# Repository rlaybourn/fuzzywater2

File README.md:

# fuzzywater
This is a masters project to create a fuzzy logic based irrigation controller for greenhouse environments
The system is based on a raspberry pi master unit and pic based slave units

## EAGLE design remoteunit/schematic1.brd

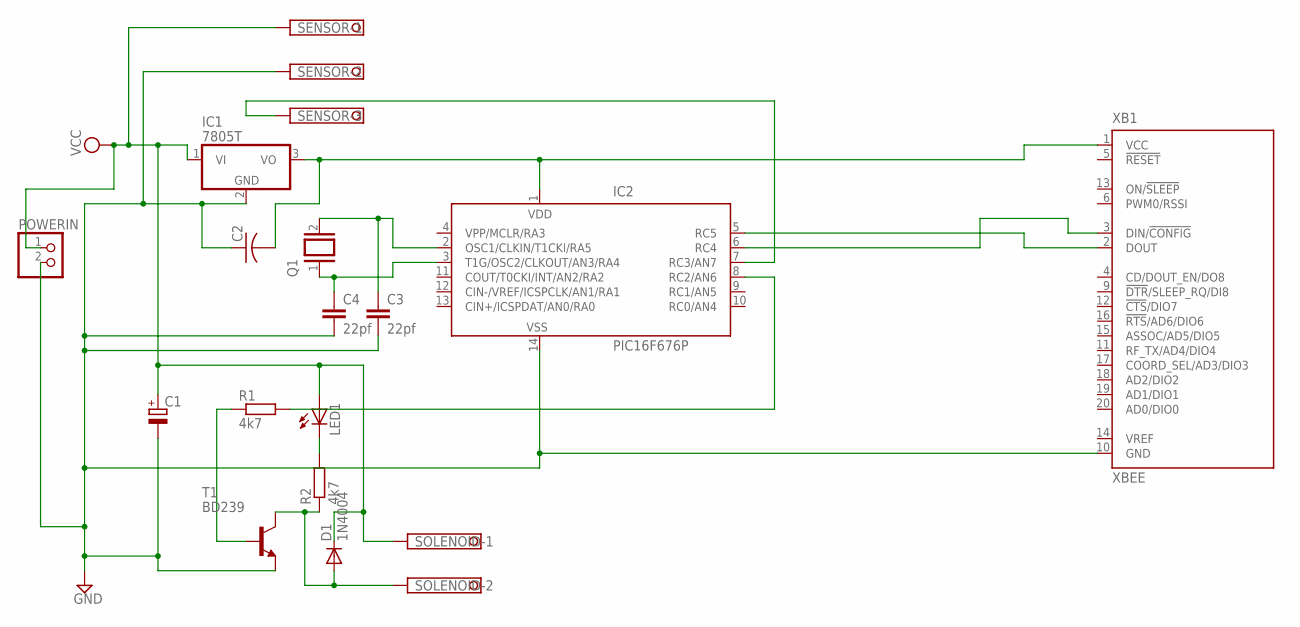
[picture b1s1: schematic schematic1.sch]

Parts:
C1: CPOL-EUE3.5-8; E3,5-8
C2: C-US050-024X044; C050-024X044
C3, C4: 22pf; C025-025X050
D1: 1N4004; DO41-10
IC1: 7805T; TO220H
IC2: PIC16F676P; DIL14
LED1: LED_ELD260; LED_LD260
POWERIN: PINHD-1X2; 1X02
Q1: XTAL; Q
R1, R2: 4k7; 0207/15
SENSOR: 1751251
SOLENOID: 1751248
T1: BD239; TO220
XB1: XBEE

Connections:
GND: C1.-, C2.1, C3.2, C4.2, IC1.2 (GND), IC2.14 (VSS), POWERIN.2, SENSOR.2, T1.3 (E), XB1.10 (GND)
unnamed: C2.2, IC1.3 (VO), IC2.1 (VDD), XB1.1 (VCC)
unnamed: IC2.8 (RC2/AN6), R1.2
unnamed: C3.1, IC2.2 (OSC1/CLKIN/T1CKI/RA5), Q1.2
unnamed: C4.1, IC2.3 (T1G/OSC2/CLKOUT/AN3/RA4), Q1.1
unnamed: IC2.5 (RC5), XB1.2 (DOUT)
unnamed: IC2.6 (RC4), XB1.3 (DIN/!CONFIG)
unnamed: D1.A, R2.1, SOLENOID.2, T1.2 (C)
unnamed: R1.1, T1.1 (B)
unnamed: LED1.K (C), R2.2
REGULATOR: IC2.7 (RC3/AN7), SENSOR.3
VCC: C1.+, D1.C, IC1.1 (VI), LED1.A, POWERIN.1, SENSOR.1, SOLENOID.1

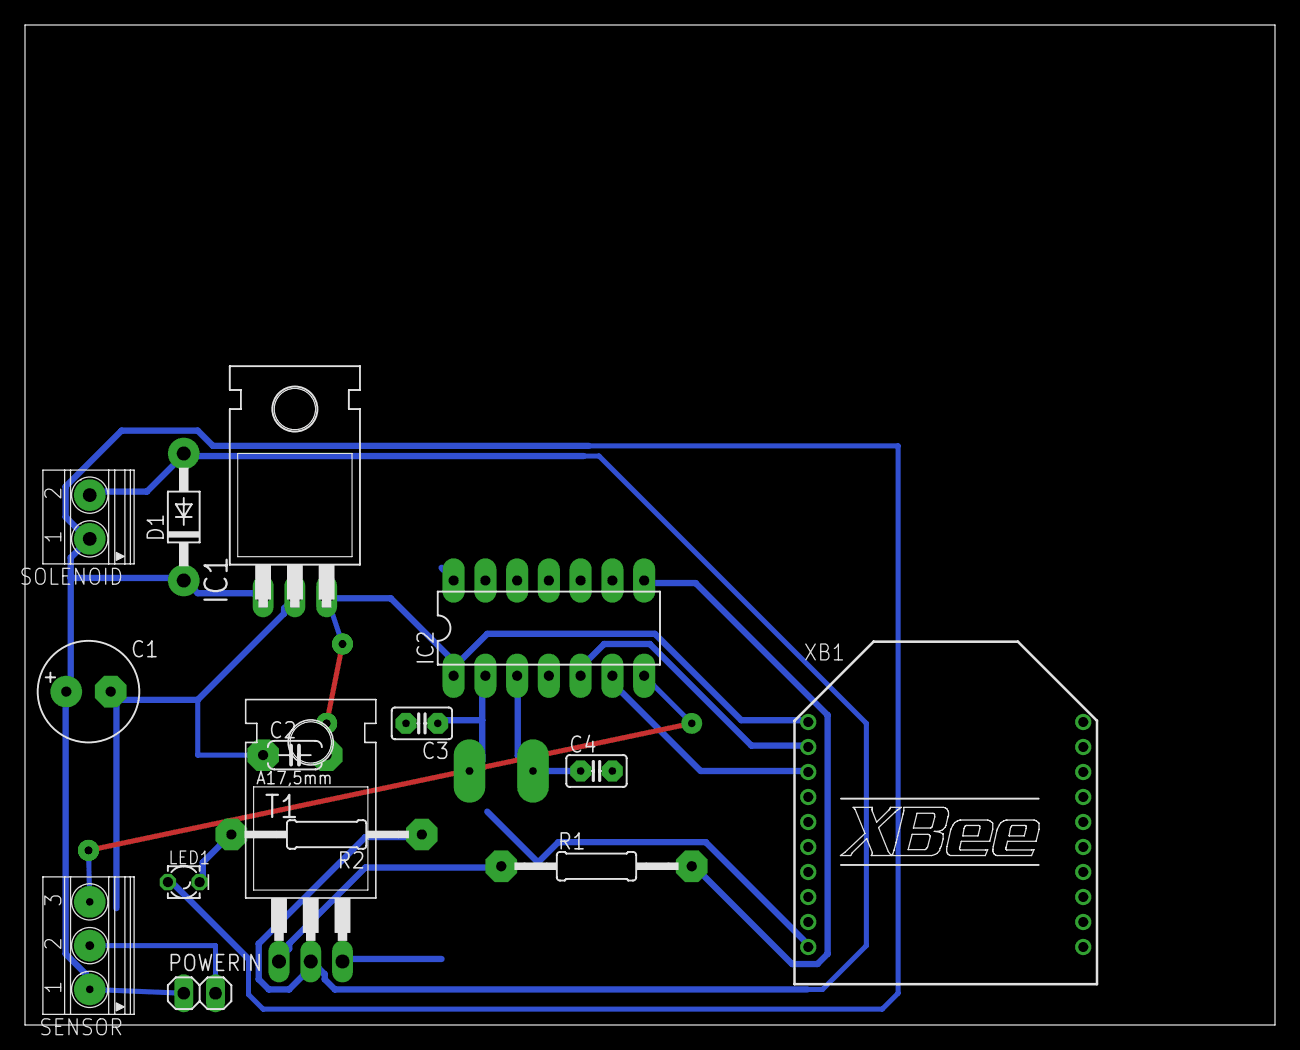
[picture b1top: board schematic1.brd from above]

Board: 2 copper layers, 100.0 x 80.0 mm, 16 parts (1 on the bottom side), 12 nets.

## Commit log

2015-09-06 updated all files in repo for submission
2015-09-06 updated some comments
